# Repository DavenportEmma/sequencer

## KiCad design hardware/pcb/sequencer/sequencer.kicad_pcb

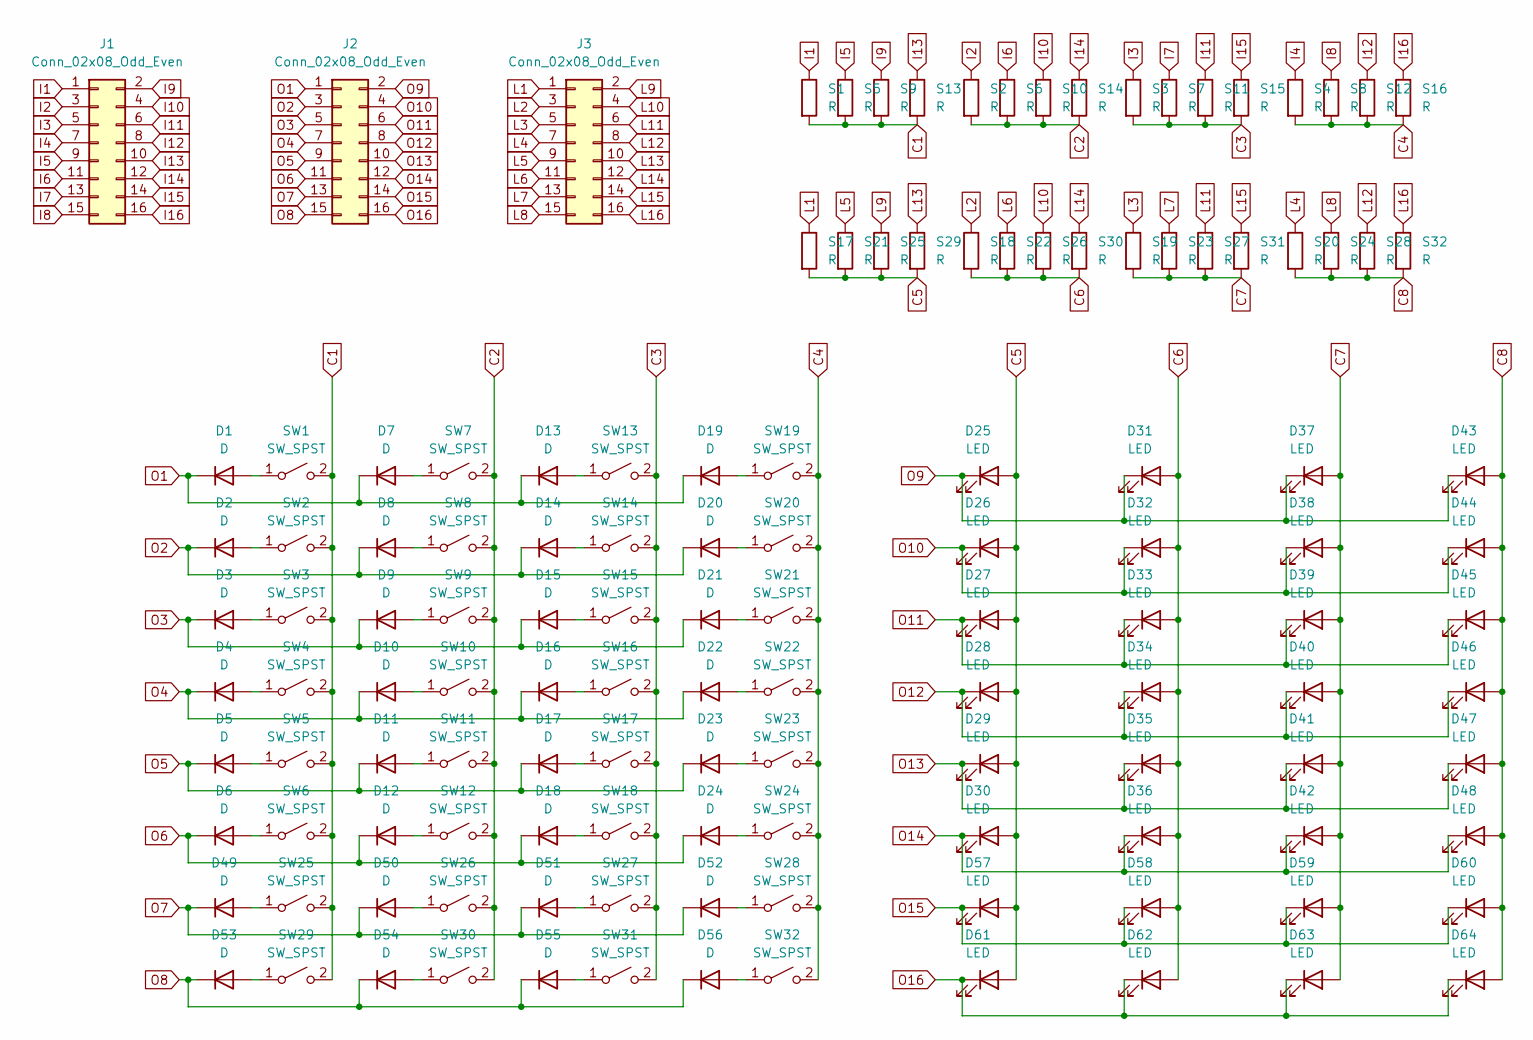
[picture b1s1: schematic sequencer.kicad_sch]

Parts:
D1, D2, D3, D4, D5, D6, D7, D8, D9, D10, D11, D12, D13, D14, D15, D16, D17, D18, D19, D20, D21, D22, D23, D24, D49, D50, D51, D52, D53, D54, D55, D56: D; D_DO-35_SOD27_P7.62mm_Horizontal
D25, D26, D27, D28, D29, D30, D31, D32, D33, D34, D35, D36, D37, D38, D39, D40, D41, D42, D43, D44, D45, D46, D47, D48, D57, D58, D59, D60, D61, D62, D63, D64: LED; LED_D3.0mm
J1, J2, J3: Conn_02x08_Odd_Even; PinHeader_2x08_P2.54mm_Vertical
S1, S2, S3, S4, S5, S6, S7, S8, S9, S10, S11, S12, S13, S14, S15, S16, S17, S18, S19, S20, S21, S22, S23, S24, S25, S26, S27, S28, S29, S30, S31, S32: R; SolderJumper-2_P1.3mm_Open_RoundedPad1.0x1.5mm
SW1, SW2, SW3, SW4, SW5, SW6, SW7, SW8, SW9, SW10, SW11, SW12, SW13, SW14, SW15, SW16, SW17, SW18, SW19, SW20, SW21, SW22, SW23, SW24, SW25, SW26, SW27, SW28, SW29, SW30, SW31, SW32: SW_SPST; SW_Cherry_MX_1.00u_PCB

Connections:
C1: S1.2, S5.2, S9.2, S13.2, SW1.2 (B), SW2.2 (B), SW3.2 (B), SW4.2 (B), SW5.2 (B), SW6.2 (B), SW25.2 (B), SW29.2 (B)
C2: S2.2, S6.2, S10.2, S14.2, SW7.2 (B), SW8.2 (B), SW9.2 (B), SW10.2 (B), SW11.2 (B), SW12.2 (B), SW26.2 (B), SW30.2 (B)
C3: S3.2, S7.2, S11.2, S15.2, SW13.2 (B), SW14.2 (B), SW15.2 (B), SW16.2 (B), SW17.2 (B), SW18.2 (B), SW27.2 (B), SW31.2 (B)
C4: S4.2, S8.2, S12.2, S16.2, SW19.2 (B), SW20.2 (B), SW21.2 (B), SW22.2 (B), SW23.2 (B), SW24.2 (B), SW28.2 (B), SW32.2 (B)
C5: D25.2 (A), D26.2 (A), D27.2 (A), D28.2 (A), D29.2 (A), D30.2 (A), D57.2 (A), D61.2 (A), S17.2, S21.2, S25.2, S29.2
C6: D31.2 (A), D32.2 (A), D33.2 (A), D34.2 (A), D35.2 (A), D36.2 (A), D58.2 (A), D62.2 (A), S18.2, S22.2, S26.2, S30.2
C7: D37.2 (A), D38.2 (A), D39.2 (A), D40.2 (A), D41.2 (A), D42.2 (A), D59.2 (A), D63.2 (A), S19.2, S23.2, S27.2, S31.2
C8: D43.2 (A), D44.2 (A), D45.2 (A), D46.2 (A), D47.2 (A), D48.2 (A), D60.2 (A), D64.2 (A), S20.2, S24.2, S28.2, S32.2
I1: J1.1, S1.1
I2: J1.3, S2.1
I3: J1.5, S3.1
I4: J1.7, S4.1
I5: J1.9, S5.1
I6: J1.11, S6.1
I7: J1.13, S7.1
I8: J1.15, S8.1
I9: J1.2, S9.1
I10: J1.4, S10.1
I11: J1.6, S11.1
I12: J1.8, S12.1
I13: J1.10, S13.1
I14: J1.12, S14.1
I15: J1.14, S15.1
I16: J1.16, S16.1
L1: J3.1, S17.1
L2: J3.3, S18.1
L3: J3.5, S19.1
L4: J3.7, S20.1
L5: J3.9, S21.1
L6: J3.11, S22.1
L7: J3.13, S23.1
L8: J3.15, S24.1
L9: J3.2, S25.1
L10: J3.4, S26.1
L11: J3.6, S27.1
L12: J3.8, S28.1
L13: J3.10, S29.1
L14: J3.12, S30.1
L15: J3.14, S31.1
L16: J3.16, S32.1
unnamed: D1.2 (A), SW1.1 (A)
unnamed: D2.2 (A), SW2.1 (A)
unnamed: D3.2 (A), SW3.1 (A)
unnamed: D4.2 (A), SW4.1 (A)
unnamed: D5.2 (A), SW5.1 (A)
unnamed: D6.2 (A), SW6.1 (A)
unnamed: D7.2 (A), SW7.1 (A)
unnamed: D8.2 (A), SW8.1 (A)
unnamed: D9.2 (A), SW9.1 (A)
unnamed: D10.2 (A), SW10.1 (A)
unnamed: D11.2 (A), SW11.1 (A)
unnamed: D12.2 (A), SW12.1 (A)
unnamed: D13.2 (A), SW13.1 (A)
unnamed: D14.2 (A), SW14.1 (A)
unnamed: D15.2 (A), SW15.1 (A)
unnamed: D16.2 (A), SW16.1 (A)
unnamed: D17.2 (A), SW17.1 (A)
unnamed: D18.2 (A), SW18.1 (A)
unnamed: D19.2 (A), SW19.1 (A)
unnamed: D20.2 (A), SW20.1 (A)
unnamed: D21.2 (A), SW21.1 (A)
unnamed: D22.2 (A), SW22.1 (A)
unnamed: D23.2 (A), SW23.1 (A)
unnamed: D24.2 (A), SW24.1 (A)
unnamed: D49.2 (A), SW25.1 (A)
unnamed: D50.2 (A), SW26.1 (A)
unnamed: D51.2 (A), SW27.1 (A)
unnamed: D52.2 (A), SW28.1 (A)
unnamed: D53.2 (A), SW29.1 (A)
unnamed: D54.2 (A), SW30.1 (A)
unnamed: D55.2 (A), SW31.1 (A)
unnamed: D56.2 (A), SW32.1 (A)
O1: D1.1 (K), D7.1 (K), D13.1 (K), D19.1 (K), J2.1
O2: D2.1 (K), D8.1 (K), D14.1 (K), D20.1 (K), J2.3
O3: D3.1 (K), D9.1 (K), D15.1 (K), D21.1 (K), J2.5
O4: D4.1 (K), D10.1 (K), D16.1 (K), D22.1 (K), J2.7
O5: D5.1 (K), D11.1 (K), D17.1 (K), D23.1 (K), J2.9
O6: D6.1 (K), D12.1 (K), D18.1 (K), D24.1 (K), J2.11
O7: D49.1 (K), D50.1 (K), D51.1 (K), D52.1 (K), J2.13
O8: D53.1 (K), D54.1 (K), D55.1 (K), D56.1 (K), J2.15
O9: D25.1 (K), D31.1 (K), D37.1 (K), D43.1 (K), J2.2
O10: D26.1 (K), D32.1 (K), D38.1 (K), D44.1 (K), J2.4
O11: D27.1 (K), D33.1 (K), D39.1 (K), D45.1 (K), J2.6
O12: D28.1 (K), D34.1 (K), D40.1 (K), D46.1 (K), J2.8
O13: D29.1 (K), D35.1 (K), D41.1 (K), D47.1 (K), J2.10
O14: D30.1 (K), D36.1 (K), D42.1 (K), D48.1 (K), J2.12
O15: D57.1 (K), D58.1 (K), D59.1 (K), D60.1 (K), J2.14
O16: D61.1 (K), D62.1 (K), D63.1 (K), D64.1 (K), J2.16

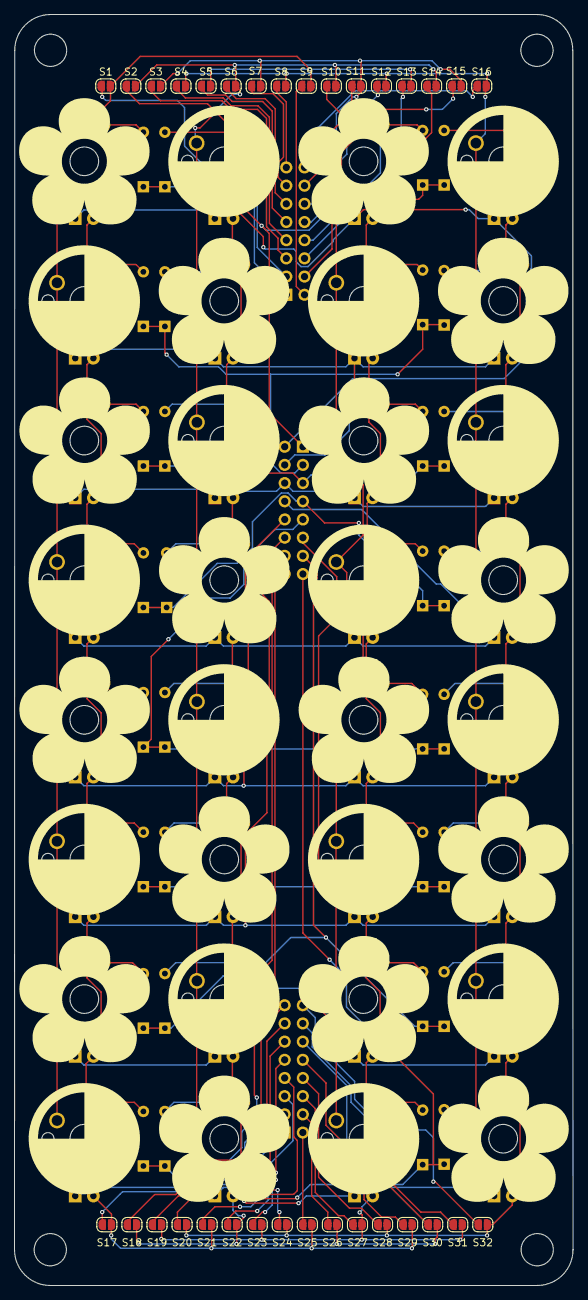
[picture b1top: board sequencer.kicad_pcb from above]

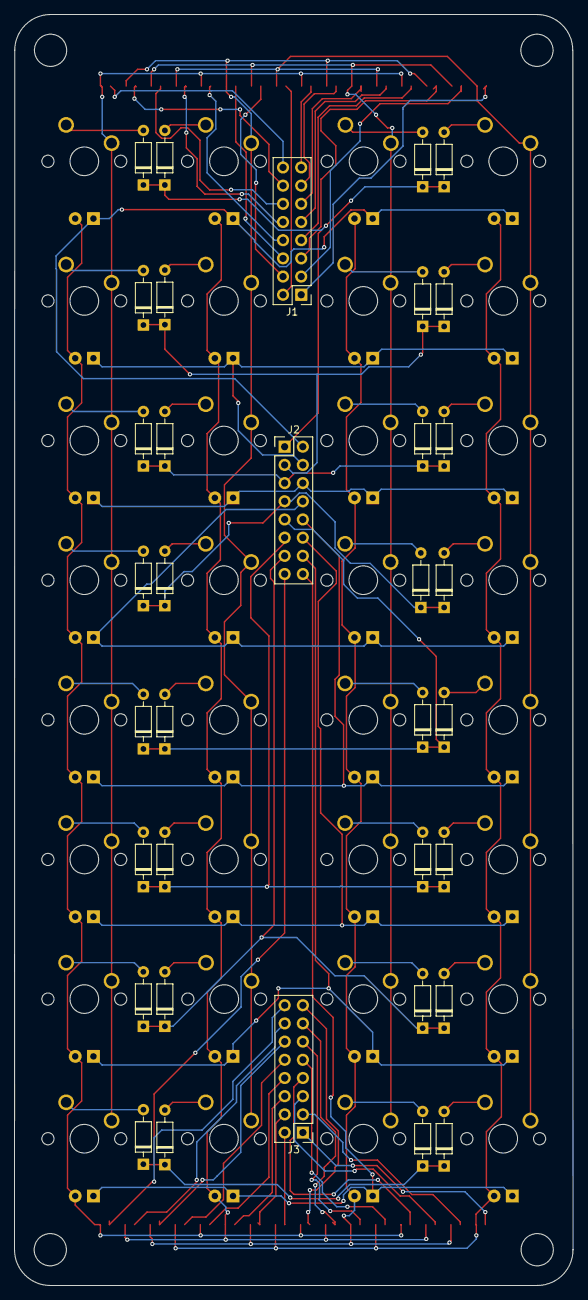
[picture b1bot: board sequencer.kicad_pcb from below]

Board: 2 copper layers, 78.0 x 177.5 mm, 131 parts (35 on the bottom side), 88 nets.

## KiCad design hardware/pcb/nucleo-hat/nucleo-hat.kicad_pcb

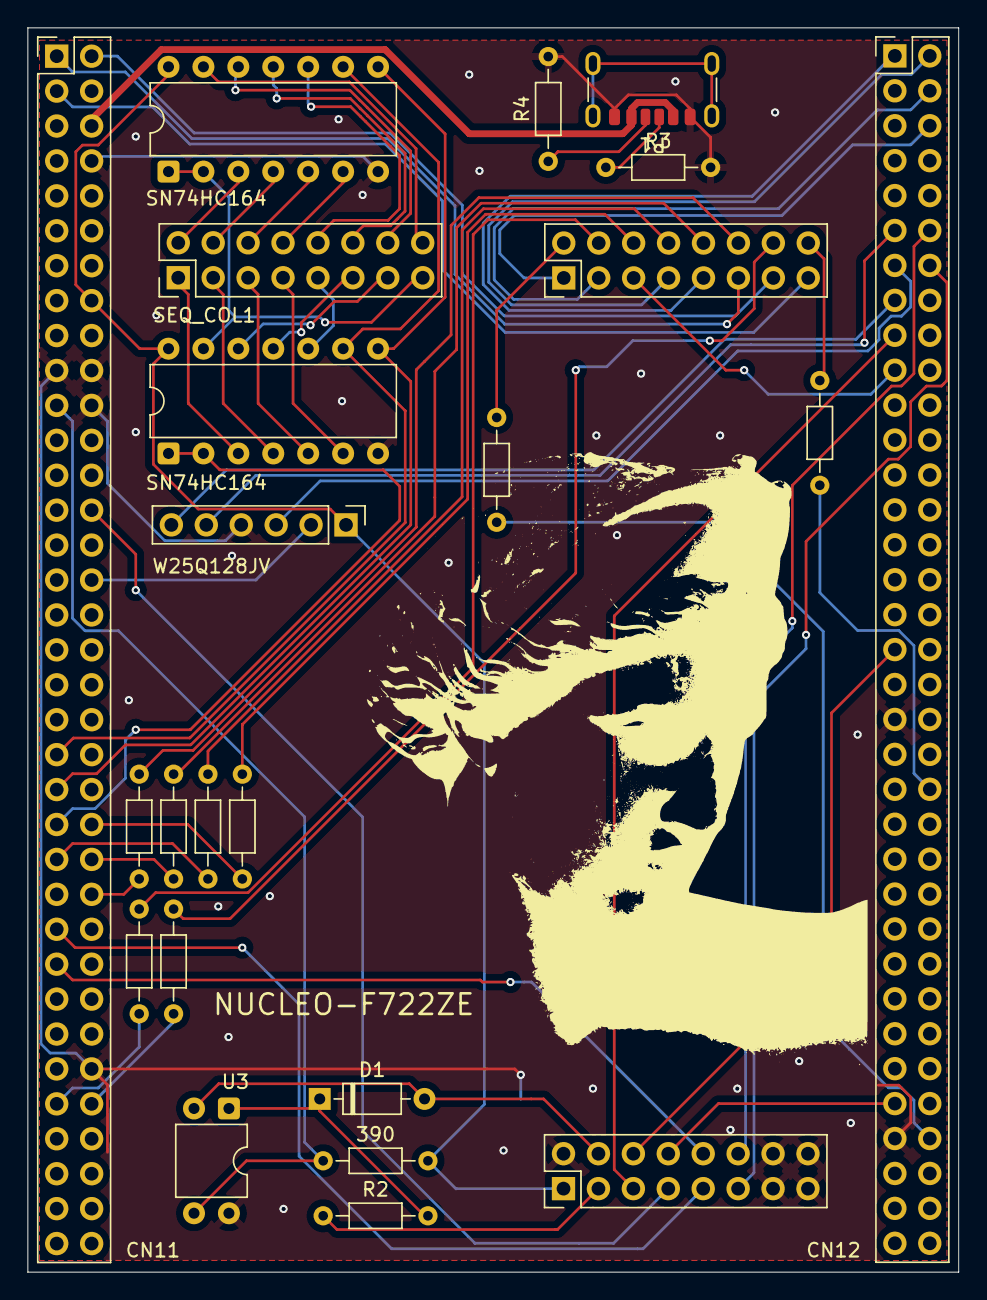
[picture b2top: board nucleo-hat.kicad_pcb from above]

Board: 2 copper layers, 67.7 x 90.5 mm, 23 parts (0 on the bottom side), 64 nets.

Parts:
390: 390; R_Axial_DIN0204_L3.6mm_D1.6mm_P7.62mm_Horizontal
CN11, CN12: Conn_02x35_Odd_Even; PinHeader_2x35_P2.54mm_Vertical
D1: D; D_DO-35_SOD27_P7.62mm_Horizontal
IO1: Conn_02x08_Odd_Even; PinHeader_2x08_P2.54mm_Vertical
P1: USB_C_Plug_USB2.0; USB_C_Receptacle_GCT_USB4125-xx-x-0190_6P_TopMnt_Horizontal
R2: 330; R_Axial_DIN0204_L3.6mm_D1.6mm_P7.62mm_Horizontal
R3, R4: 1K5; R_Axial_DIN0204_L3.6mm_D1.6mm_P7.62mm_Horizontal
R5, R6, R7, R8, R9, R10, R11, R12: R; R_Axial_DIN0204_L3.6mm_D1.6mm_P7.62mm_Horizontal
SEQ_COL1: Conn_02x08_Odd_Even; PinHeader_2x08_P2.54mm_Vertical
SEQ_ROW1: Conn_02x08_Odd_Even; PinHeader_2x08_P2.54mm_Vertical
SN74HC164, SN74HC164#2: 74HC164; DIP-14_W7.62mm
U3: SFH617A-1; DIP-4_W7.62mm
W25Q128JV : Conn_01x06; PinHeader_1x06_P2.54mm_Vertical

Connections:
3.3: 390.2, CN11.16, IO1.1, SN74HC164.14 (VCC), SN74HC164#2.14 (VCC), W25Q128JV.1
E5V: CN11.6, P1.A9 (VBUS), P1.B9 (VBUS)
GND: CN11.8, CN11.19, CN11.20, CN11.22, CN11.60, CN12.39, CN12.63, IO1.2, IO1.13, IO1.14, IO1.15, IO1.16, P1.A12 (GND), P1.B12 (GND), R3.2, R4.2, SN74HC164.7 (GND), SN74HC164#2.7 (GND), U3.4, W25Q128JV.4
MIDI_IN_GND: D1.2 (A), IO1.4, U3.2
MIDI_IN_SRC: IO1.3, R2.1
unnamed: D1.1 (K), R2.2, U3.1
unnamed: P1.A5 (CC), R3.1
unnamed: P1.B5 (VCONN), R4.1
unnamed: SEQ_COL1.1, SN74HC164#2.3 (Q0)
unnamed: SEQ_COL1.2, SN74HC164.3 (Q0)
unnamed: SEQ_COL1.3, SN74HC164#2.4 (Q1)
unnamed: SEQ_COL1.4, SN74HC164.4 (Q1)
unnamed: SEQ_COL1.5, SN74HC164#2.5 (Q2)
unnamed: SEQ_COL1.6, SN74HC164.5 (Q2)
unnamed: SEQ_COL1.7, SN74HC164#2.6 (Q3)
unnamed: SEQ_COL1.8, SN74HC164.6 (Q3)
unnamed: SEQ_COL1.9, SN74HC164#2.10 (Q4)
unnamed: SEQ_COL1.10, SN74HC164.10 (Q4)
unnamed: SEQ_COL1.11, SN74HC164#2.11 (Q5)
unnamed: SEQ_COL1.12, SN74HC164.11 (Q5)
unnamed: SEQ_COL1.13, SN74HC164#2.12 (Q6)
unnamed: SEQ_COL1.14, SN74HC164.12 (Q6)
unnamed: SEQ_COL1.16, SN74HC164.13 (Q7)
unnamed: R5.1, SEQ_ROW1.2
unnamed: R6.1, SEQ_ROW1.4
unnamed: R7.1, SEQ_ROW1.6
unnamed: R8.1, SEQ_ROW1.8
unnamed: R9.1, SEQ_ROW1.10
unnamed: R10.1, SEQ_ROW1.12
unnamed: R11.1, SEQ_ROW1.14
unnamed: R12.1, SEQ_ROW1.16
PA0: CN11.28, IO1.7
PA2: CN12.35, IO1.6
PA4: CN11.32, W25Q128JV.2
PA5: CN12.11, W25Q128JV.5
PA6: CN12.13, W25Q128JV.3
PA7: CN12.15, W25Q128JV.6
PA11: CN12.14, IO1.11
PA12: CN12.12, IO1.12
PB6: CN12.17, IO1.5
PB7: 390.1, CN11.21, U3.3
PC5: CN12.6, SEQ_ROW1.1
PC6: CN12.4, SEQ_ROW1.3
PC7: CN12.19, SEQ_ROW1.5
PC8: CN12.2, SEQ_ROW1.7
PC9: CN12.1, SEQ_ROW1.9
PC10: CN11.1, SEQ_ROW1.11
PC11: CN11.2, SEQ_ROW1.13
PC12: CN11.3, SEQ_ROW1.15
PD5: CN11.41, SN74HC164.9 (~MR), SN74HC164#2.9 (~MR)
PD6: CN11.43, SN74HC164.8 (CP), SN74HC164#2.8 (CP)
PD7: CN11.45, SN74HC164#2.1 (DSA), SN74HC164#2.2 (DSB)
PE0: CN12.64, R5.2
PE1: CN11.61, R6.2
PE2: CN11.46, R7.2
PE3: CN11.47, R8.2
PE4: CN11.48, R9.2
PE5: CN11.50, R10.2
PE6: CN11.62, R11.2
PE7: CN12.44, R12.2
PF0: CN11.53, IO1.10
PF1: CN11.51, IO1.9
PG14: CN12.61, IO1.8
Q8: SEQ_COL1.15, SN74HC164.1 (DSA), SN74HC164.2 (DSB), SN74HC164#2.13 (Q7)

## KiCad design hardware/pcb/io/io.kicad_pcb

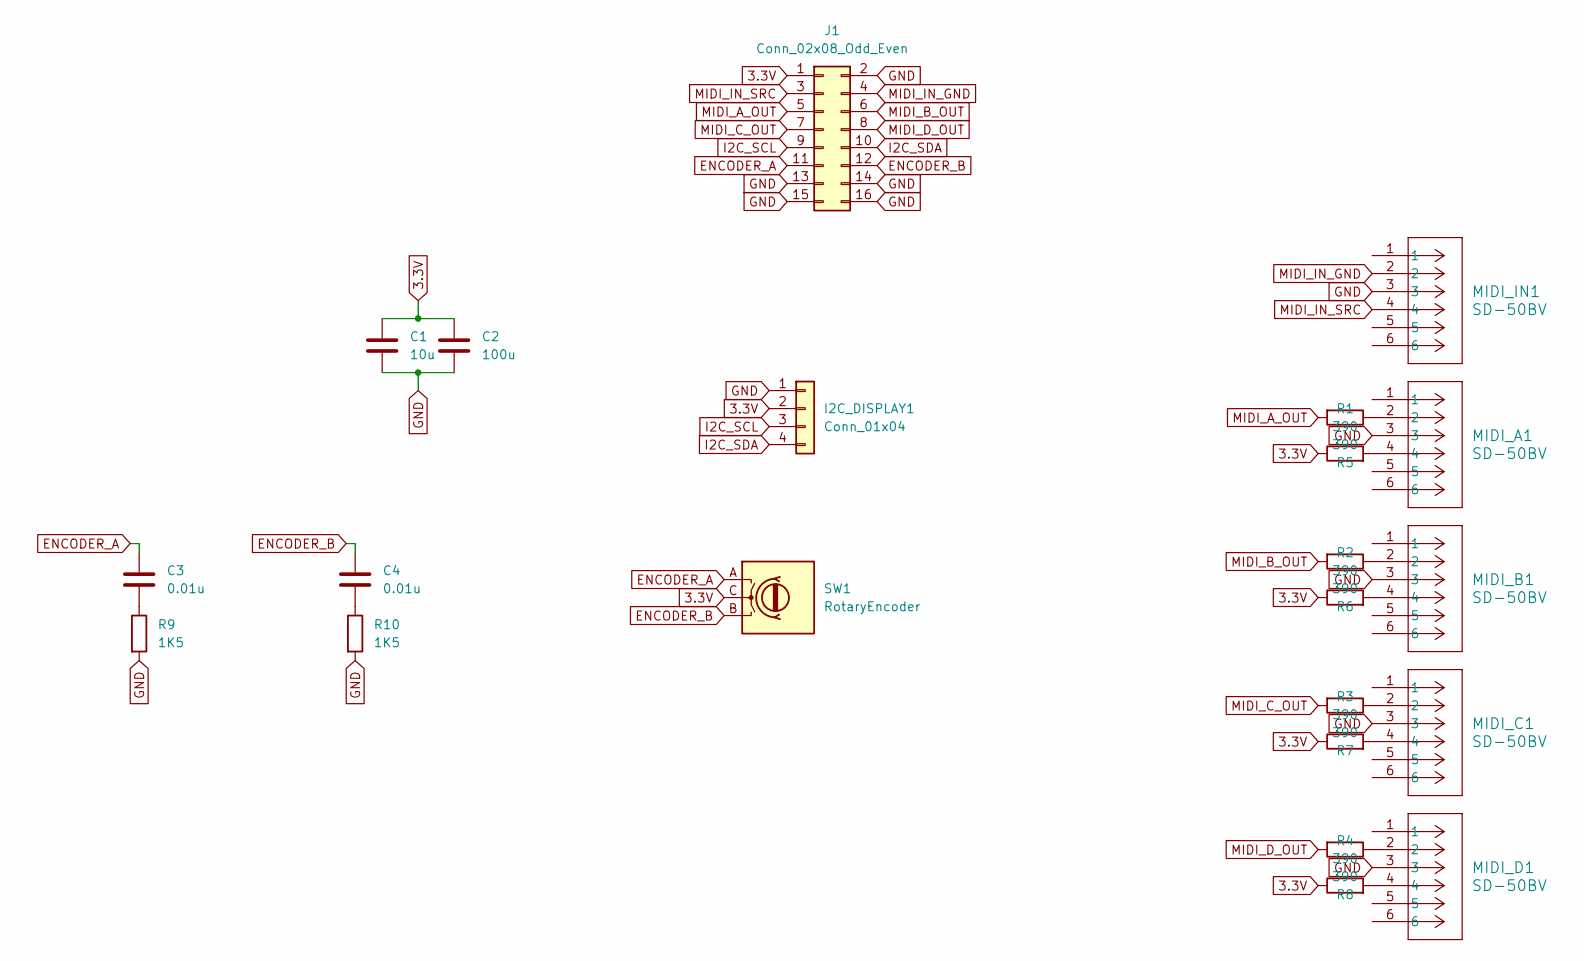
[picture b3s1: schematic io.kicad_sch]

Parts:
C1: 10u; CP_Radial_D5.0mm_P2.50mm
C2: 100u; CP_Radial_D5.0mm_P2.50mm
C3, C4: 0.01u; CP_Radial_D5.0mm_P2.50mm
I2C_DISPLAY1: Conn_01x04; PinHeader_1x04_P2.54mm_Vertical
J1: Conn_02x08_Odd_Even; PinHeader_2x08_P2.54mm_Vertical
MIDI_A1: SD-50BV; CONN6_SD-50BV_CUD
MIDI_B1: SD-50BV; CONN6_SD-50BV_CUD
MIDI_C1: SD-50BV; CONN6_SD-50BV_CUD
MIDI_D1: SD-50BV; CONN6_SD-50BV_CUD
MIDI_IN1: SD-50BV; CONN6_SD-50BV_CUD
R1, R2, R3, R4, R5, R6, R7, R8: 390; R_Axial_DIN0207_L6.3mm_D2.5mm_P10.16mm_Horizontal
R9, R10: 1K5; R_Axial_DIN0207_L6.3mm_D2.5mm_P10.16mm_Horizontal
SW1: RotaryEncoder; Bourns-PEC11R-4220F-S0024-0-0-0

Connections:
3.3V: C1.1, C2.1, I2C_DISPLAY1.2, J1.1, R1.1, R2.1, R3.1, R4.1, SW1.C
ENCODER_A: C3.1, J1.11, SW1.A
ENCODER_B: C4.1, J1.12, SW1.B
GND: C1.2, C2.2, I2C_DISPLAY1.1, J1.2, J1.13, J1.14, J1.15, J1.16, MIDI_A1.3, MIDI_B1.3, MIDI_C1.3, MIDI_D1.3, MIDI_IN1.3, R9.2, R10.2
I2C_SCL: I2C_DISPLAY1.3, J1.9
I2C_SDA: I2C_DISPLAY1.4, J1.10
MIDI_A_OUT: J1.5, R5.2
MIDI_B_OUT: J1.6, R6.2
MIDI_C_OUT: J1.7, R7.2
MIDI_D_OUT: J1.8, R8.2
MIDI_IN_GND: J1.4, MIDI_IN1.2
MIDI_IN_SRC: J1.3, MIDI_IN1.4
unnamed: C3.2, R9.1
unnamed: C4.2, R10.1
unnamed: MIDI_A1.2, R5.1
unnamed: MIDI_A1.4, R1.2
unnamed: MIDI_B1.2, R6.1
unnamed: MIDI_B1.4, R2.2
unnamed: MIDI_C1.2, R7.1
unnamed: MIDI_C1.4, R3.2
unnamed: MIDI_D1.2, R8.1
unnamed: MIDI_D1.4, R4.2

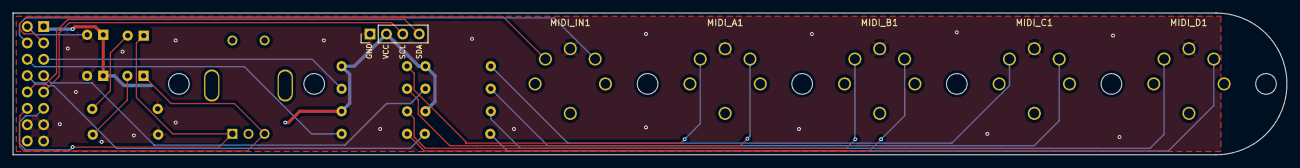
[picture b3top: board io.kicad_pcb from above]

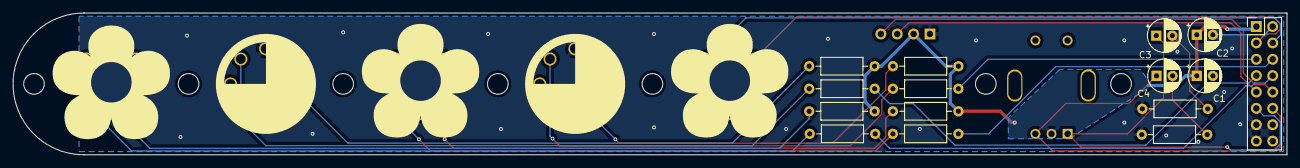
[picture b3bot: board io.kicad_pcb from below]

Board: 2 copper layers, 197.8 x 22.0 mm, 22 parts (15 on the bottom side), 22 nets.

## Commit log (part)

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2025-01-15 sequencer: route pcb
2025-01-15 gitignore: ignore lock files
2025-01-16 controls: add pcb design for note control keys
2025-02-09 and so it begins...
    big dog commit for basic keyscan task
2025-02-14 main: remove references to menu task
    the menu handling will be done from the key scan task as that is where
    user inputs are processed. dealing with messages being passed between
    tasks is going to take too much time and slow project momentum
2025-02-14 menu: implement state machine for keyboard
2025-02-14 tasks: pass user input to menu handler
2025-02-16 menu: add arg to state functions
    add an argument to state functions so that they can modify the active
    step and active sequence global variables
2025-02-16 menu: make state functions static
    make the internal state functions static
2025-03-03 tasks: formatting :)
2025-03-03 CMakeLists: include sequence.c in compilation
2025-03-03 menu: func to convert keys to sequence ids
    converts a key to a sequence or step number this is needed as the key
    representing the first step/sequence is not key 0
2025-03-03 tasks: call play_sequences()
    this function reads midi data from the flash chip and sends to uart
2025-03-15 main: update task priorities
2025-03-15 setup: add erase chip option on start up
    for testing purposes if you hold a key down as the sequencer starts it
    will erase the entire chip
2025-03-15 sequence: update includes
2025-03-15 sequence: turn off notes on sequence disable
    this prevents a note from ringing out when a sequence is turned off
2025-03-15 sequence: set channel on sequence enable
    read the sequence channel on enable
2025-03-15 tasks: remove unused variable
2025-03-21 sequence: def STEP_MAX_BYTES, ALL_STEPS_MAX_BYTES
    STEP_MAX_BYTES is the max number of bytes one step
    data can be (see MEMORY.md)
    ALL_STEPS_MAX_BYTES is simply the maximum bytes
    per step times the maximum sequence length (max
    steps per sequence)
2025-03-21 sequence: replace buffer_max with preproc def
2025-03-28 hardware: add kicad project
2025-03-28 main: declare mutex for edit buffer
2025-03-28 main: declare mutexes before setup()
2025-03-28 menu: reset step edit buffer on main menu
    and set the buffer ready flag to zero
2025-03-28 common: add file for common pre proc defs
2025-03-28 sequence: update pre proc def names
    STEP_MAX_BYTES to BYTES_PER_STEP
    ALL_STEPS_MAX_BYTES to BYTES_PER_SEQ
2025-03-28 menu: make key 16b int for more flexibility
2025-03-28 menu: add state for previous state management
2025-03-28 sequence: reoganise code
2025-03-28 sequence: include common.h
2025-03-28 menu: handle automatic transitions
2025-03-28 step_edit: file for step_edit_buffer functions
2025-03-28 menu: add step note edit event
2025-03-28 menu: add S_ST_NOTE functionality
2025-03-28 menu: update prints
2025-03-28 sequence: refactor for better readabiltiy
2025-03-28 step_edit: fix bug in editing a note
    the note update function puts the new note value in the NOTE_OFF section
    of the next step. I was accidentally putting it in the NOTE_ON section
2025-03-28 menu: remove old includes
2025-03-31 menu: only reset edit buffer if SQ_EDIT_READY
    prevents eronious calls to reset buffer
2025-04-11 hardware: add schematics
    add controls, io, keys, and nucleo hat boards
2025-04-17 src: change sq_states to sequences
    I think the name sq_states didn't reflect accurately what this array
    was being used for
2025-04-17 menu: include step edit buffer
2025-04-18 m_buf: implement vector buffer for midi notes
    I could make k_buf type agnostic but the only thing I'm optimising for
    is project completion so we're rolling with this for the moment
2025-04-18 tasks: use buffers to synchronise notes
    instead of playing notes as sequences are being processed load the notes
    into a buffer then sending all notes over midi at the same time
2025-04-18 sequence: handle playing empty sequences
    the read_step function will return a 1 if the note read from memory is
    malformed. this should stop the sequencer from pushing out nonsense over
    midi
2025-04-19 Kconfig: add project specific configurations
2025-04-19 sequence: reset step counter to 0 on disable
    this can be switched on or off using RESET_SEQ_ON_DISABLE kconfig option
2025-04-19 CMakeLists: add step_editor to src list
2025-04-19 menu: initialise kbuf for midi rx
    this will be filled with data in the usart rx interrupt handler
2025-04-19 tasks: fix tempo divisor
    the tempo divisor was too high
2025-04-19 Kconfig: add ENABLE_STARTUP_MEMORY_CLEAR
    enable the ability to delete the entire flash memory by holding a key on
    startup
2025-04-23 step_editor: add mute step functionality
    toggle the muted state for a step
2025-04-23 menu: add mute step state to state machine
2025-04-23 sequence: add disable_sequence function
2025-04-23 menu: add change midi channel menu state handler
2025-04-23 rotary_encoder: add driver for encoder
2025-04-23 setup: initialise io for rotary encoder
2025-04-23 sequence: change get_channel() to read_channel()
    I wanted a public function called get_channel() read_channel() is static
    and for reading from flash memory
2025-04-23 rotary_encoder: reverse direction
    how I've set the encoder up was incrementing on anti clockwise
2025-04-23 main: reflect changes in setup()
2025-04-23 sequence: fix enabling sequence
    it wasn't enabling the sequence 😲
2025-04-23 menu: change midi channel with rotary encoder
2025-04-23 step_editor: toggle_step prototype 🤖
2025-04-24 sequence: change note counter incrementation
    increment the counter after all the stuff has been done with the notes
2025-04-25 step_editor: update midi note step_editor
    when changing a note with an external midi controller only log the
    actual midi event received instead of assuming a note off event for the
    next step
2025-04-25 step_editor: add edit_step_velocity function
2025-04-25 menu: edit velocity on encoder movement
2025-04-25 sequencer: add flower and circle decals
2025-04-25 sequencer: move keys closer together
2025-04-29 step_editor: add clear step function
2025-05-01 software: remove autoconf, stm32f722xx
    remove the inclusion of thee files and include them via compiler flags.
    this will make it easier to support other devices
2025-05-02 step_editor: return status byte from edit note
    this lets the state machine know if it should advance to the next step
    if the status is a NOTE_ON byte
2025-05-03 menu: use active_st advance and retreat funcs
2025-05-03 menu: handle sequence clear button press
2025-05-03 sequence: call get_step_data_offset()
    when reading a step from memory for the first time we don't know the
    address of the step data for the sequence. call get_step_data_offset to
    find this
2025-05-03 step_edit_buffer: increment step sector offset
    after loading the edit buffer, increment the step data sector offset
2025-05-03 flash: add wrappers for flash chip functions
    the wrappers let me use mutexes with platform code
2025-05-03 sequence: use flash wrappers
    use flash wrappers to protect spi flash chip access
2025-05-04 setup: use kb_handle_t instead of kbuf
2025-05-05 menu: add ctrl and shift buttons
2025-05-05 menu: remove SQ from shift, ctrl event enums
    these keys aren't restricted to sequence operations
2025-05-05 sequence: use check_bit from util
2025-05-05 menu: use MSEL_MASK to identify multi selection
2025-05-05 sequence: add toggle_sequences()
    this function takes the sequence selection mask and toggles all the
    sequences that are selected
2025-05-06 menu: clean up extraneous uart sends
2025-05-08 nucleo-hat: make updates after getting board
2025-05-15 sequence: remove redundant mutex use
2025-05-15 main: initialise st_mask_mutex
2025-05-18 step_edit_buffer: improve edit_buffer_load mutexes
2025-05-18 Kconfig: add AUTO_INC_STEP_ON_MIDI_IN
    setting this to yes advances the sequencer to the next step when editing
    a sequence and a midi in signal is received
2025-05-18 step_editor: add polyphony for edit step velocity
    change the velocity for all notes in the step
2025-05-19 step_editor: overhaul edit step note for polyphony
    handle both midi in and 13 key keyboard events in the same function
2025-05-28 ascii: add font file for ssd1306
2025-05-28 proj: include i2c and ssd1306 drivers
2025-05-28 setup: initialise i2c and ssd1306
2025-05-28 display: add num_to_str
    this function takes number n, and char array s and converts the number
    to a string compatible with the ssd1306 driver
2025-05-28 sequence: expose bytes_to_step
2025-05-28 sequence: refactor bytes_to_step
2025-06-22 menu: move menu button
2025-10-14 MEMORY: update docs
2025-10-19 common: remove unused BYTES_PER_SEQ
2025-10-19 flash: reflect updates to flash driver in platform
    change the read length for spi read from 16b to 32b for longer reads
2025-10-19 src: read all sequences from ram
    I apologise for this massive commit but I'm so tired and if I don't do
    this now I think I'll die
    on startup read all sequence data from the flash chip into structures
    in ram. this removes the need for the step edit buffer and significantly
    improves performance with a downside being larger memory requirements
    but at this point I just want to get this project over and done with so
2025-10-28 menu: add sequence queuing functionality
2025-11-01 setup: remove use of malloc for display buffer
    we can statically allocate this as we're never going to need to de-alloc
    this memory
2025-11-01 util: add clear_bit() function
    this clears a bit from an array of fields
2025-11-01 sequence: fix problem with out of sync queueing
    update load_sequences to start playing any sequences that have been
    queued but have not been enabled yet
2025-11-01 step_editor: remove mutex use
    i'm probably going to regret this
2025-11-01 sequence: get rid of mutexes
    :)
2025-11-02 sequence: handle first step disabled error
    if the first step of the sequence is disabled it wasn't properly queuing
    or breaking. this fixes that
2025-11-08 menu: use separate masks for step and sq select
2025-11-09 main: intialise all midi ports
2025-11-09 tasks: handle multiple midi out ports
    add an individual buffer for each port's note off and note on data
2025-11-09 sequence: handle all steps disabled
    advance onto the next enabled step, skipping any disabled steps. when this
    step is found, update the counter, and return 0. if we have looped the
    entire way back to where we began without finding an enabled step, break the
    loop and return 1
2025-11-11 menu: add tempo changing capabilities
2025-11-11 sequence: clean up sequence queue logic
2025-11-12 menu: fix type error
2025-11-13 menu: add tempo prescale for sequences
    this allows a sequence to play slower than the system tempo
2025-11-13 sequence: add support for tempo prescaler
2025-11-13 menu: play notes when stepping through sq
2025-11-16 util: add find first and last bit functions
    these return the first and last set bit of a field, respectively
2025-11-16 display: update to use new 16px characters
2025-11-16 sequence: handle disabled step bug
    previously an all notes off signal was not being sent to the synth if
    there was a disabled step present in the sequence
2025-11-23 sequence: erase entire chip before save
    instead of erasing sectors, nuke the whole chip. this was causing errors
    where not all the sequence data was being saved
2025-11-29 menu: allow sq_clear from more states
2025-11-29 menu: display step velocity when editing st vel
2025-12-07 display: add error handling for clear_line
    this prevents buffer overflows
2025-12-07 menu: implement copy and paste for steps
2025-12-07 step_edit_buffer: rename to avoid confusion
2025-12-10 step_editor: remove msb flagging for note_off
    this was a good idea but i need to remove it for the moment
2025-12-10 menu: implement sq copy and paste
2025-12-13 step_editor: remove note msb masking
    the note_on/note_off circular buffers need to be redesigned from the
    ground up
2025-12-15 tasks: update uart task params
    pass the pointer for the usart port directly to the task instead of
    a numerical representation
2025-12-15 util: fix off by one error in find last bit
2025-12-15 main: add save task to scheduler
2025-12-15 sequence: save prescaler data for each sequence
2025-12-15 menu: add conditional st_menu play note
    if CONFIG_PLAY_ST_MENU_NOTE is set, play the note for a step
2025-12-20 menu: switch output port for ext midi controller
    depending on which sequence is active, switch the output port
2026-01-01 sequence: save additional sequence metadata
    add prescale value and enabled steps to the sequence metadata saved
